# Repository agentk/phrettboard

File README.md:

# Phrettboard v1

A simple split staggered colluminar layout ergonomic keyboard.

Design priorities:

- Wireless - Bluetooth with excellent battery life
- Compact - Small and light enough to travel while chunky enough to stay put on the desk
- Tenting - Slight tenting with ability to adjust tenting in post
- Travel - Able to throw in a backpack daily for work

## Project files and folders

The repo is essentially ergogen and zmk smashed together with little regard for preserving the GitHub actions support for the ZMK config.

## BOM

| Item | Quantity |
| --- | --- |
| M3x10 BHCS | 4 |
| M3x20 BHCS | 4 |
| [LiPo Battery 2000mAh 3.7V 113450](https://ecocell.com.au/product/lipo-2000-113450/) | 2 |
| PCB | 1 pair |
| Kailh Choc hotswap sockets | 38 |
| Kailh Choc switches of your choice | 38 |
| Keycaps of your choice to match (1U) | 38 |
| Diodes IN4148 SOD-123 | 38 |
| JST-PH 2P Side entry socket | 2 |
| Silicone dome feet 8.8mm x 2.5mm | 10 |
| NRF82840 or Nice Nano v2 dev board | 2 |
| Pin sockets - machine pin - 12pin | 4 |
| Pin headers - machine pin - 12pin | 4 |
| Nice!view LCD display | 2 |
| Pin sockets - machine pin - 5pin | 2 |
| Pin headers - machine pin - 5pin | 2 |
| EVQPUC02K 4.7*3.5*1.65 SMD Reset button | 2 |
| MSS3 SMD Sliding power switch | 2 |

## [Ergogen](https://github.com/ergogen/ergogen)

The keyboard layout is built in Ergogen, then routed in Kicad.

To modify the layout:

```shell
cd ergogen
make
```

This will generate files into the `ergogen/output/` folder for both outlines and PCBs. It will overwrite any existing routed PCBs and will require you to reroute again.

## 3D Printing

The 3D printed parts were generated in Fusion 360 based off the PCB step file exported from Kicad. The priority was a form fitting case with some minor tenting which conveniently worked out well to allow space underneath for a large battery alongside the controller. The two inner feet can also be removed to reveal extra heatset inserts that support using M3 screws to increase the hight for extra tenting.

The glamour shots all featue cases FDM printed in ABS and resing printed keycaps. If you decide to print your own keycaps check out [KLP Lame](https://www.printables.com/model/552557-klp-lame-kailh-low-profile-choc-keycaps) for good sculpted keycaps (designed for resin) and [Nijuni Keycaps](https://www.printables.com/model/429659) for flatter keycaps (designed for FDM).

If printing the case in ABS I recommend using scaling X & Y by 100.5% to compensate for material shrinkage.

The travel case is designed to be printed in TPU. It prints well in quite flexible TPU and has a lot of give in it. If printing in a different material you will most likely need to scale the model bigger or smaller.

## [ZMK firmware](https://zmk.dev/docs)

To setup the build environment with Docker installed, run:

```shell
cd zmk-config
./zmk.sh build-docker
```

The typical workflow to modify the keymap is to use the [keymap editor](https://nickcoutsos.github.io/keymap-editor/), select the Clipboard source with keyboard type of custom, paste in the contents of `zmk-config/boards/shields/phrett/phrett.json` into the layout field and `zmk-config/boards/shields/phrett/phrett.keymap` into the keymap field. Modify the keyboard layout as desired, click 'Copy updated keymap' and paste it back into the local keymap.

From there the firmware can be rebuilt using:

```shell
cd zmk-config
make
```

Then connect each keyboard half one at a time, put them into bootloader mode by double tapping reset, then copying to approperate firmware from `zmk-config/artifacts/phrett_{left,right}.uf2` to the now mounted controller volume.

## License

<p xmlns:cc="http://creativecommons.org/ns#" xmlns:dct="http://purl.org/dc/terms/"><a property="dct:title" rel="cc:attributionURL" href="https://github.com/agentk/phrettboard">Phrettboard v1</a> by <a rel="cc:attributionURL dct:creator" property="cc:attributionName" href="https://github.com/agentk">Karl Bowden</a> is licensed under <a href="https://creativecommons.org/licenses/by-sa/4.0/?ref=chooser-v1" target="_blank" rel="license noopener noreferrer" style="display:inline-block;">CC BY-SA 4.0</a></p>

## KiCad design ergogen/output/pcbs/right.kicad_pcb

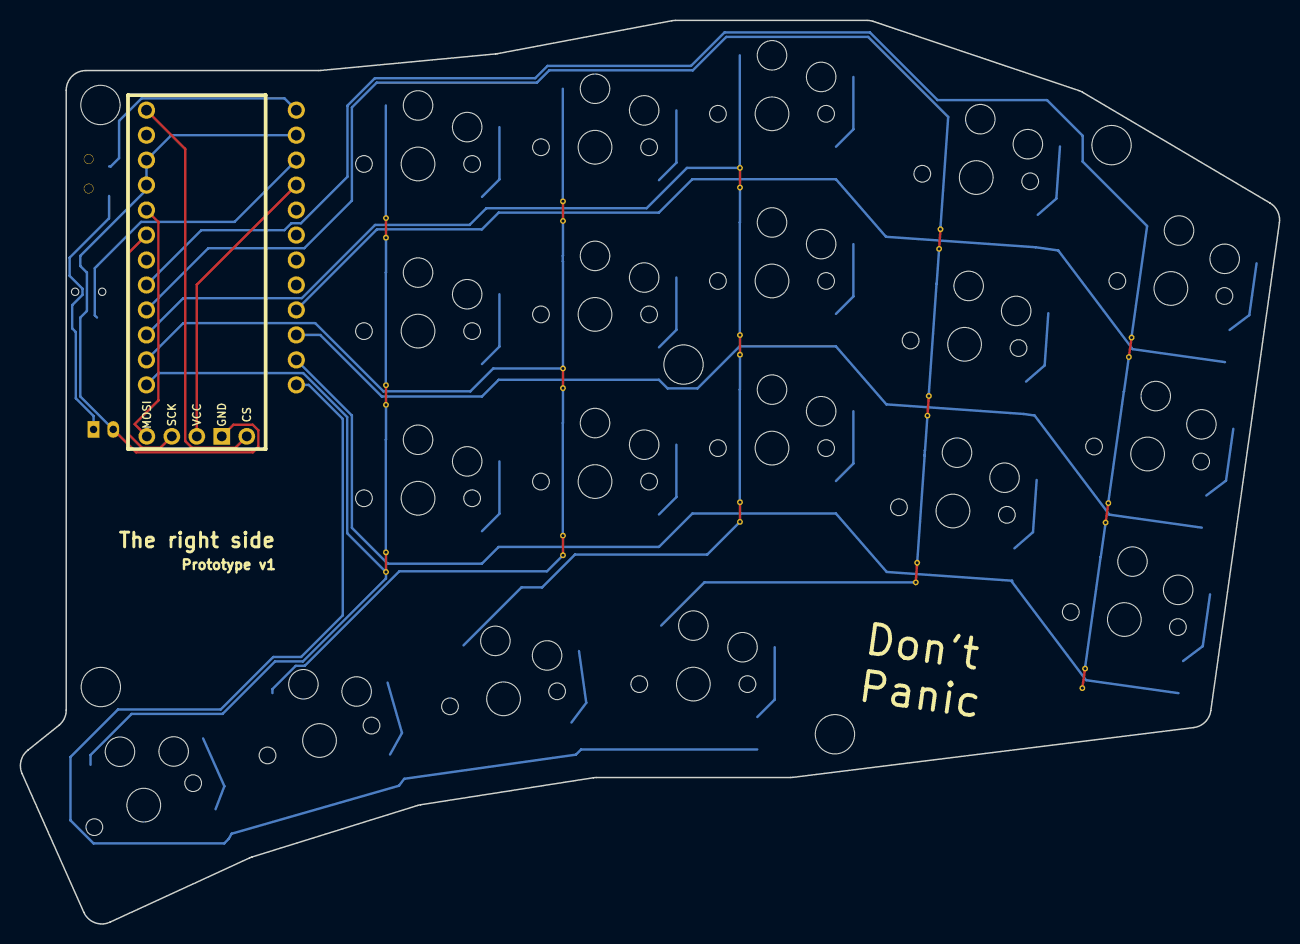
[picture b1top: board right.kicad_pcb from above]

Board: 2 copper layers, 128.1 x 91.9 mm, 43 parts (0 on the bottom side), 36 nets.

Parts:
B1: Panasonic_EVQPUL_EVQPUC
D1, D2, D3, D4, D5, D6, D7, D8, D9, D10, D11, D12, D13, D14, D15, D16, D17, D18, D19: ComboDiode
JST1: JST_PH_S2B-PH-K_02x2.00mm_Angled
MCU1: nice_nano
S1, S2, S3, S4, S5, S6, S7, S8, S9, S10, S11, S12, S13, S14, S15, S16, S17, S18, S19: PG1350
T1: SPDT_C128955
niceView1: niceView; niceView_headers

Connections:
GND: B1.1, JST1.2, MCU1.3, MCU1.4, MCU1.23, niceView1.2
P006: MCU1.1, niceView1.1
P009: D16.1, D17.1, D18.1, D19.1, MCU1.13
P010: D1.1, D4.1, D7.1, D10.1, D13.1, MCU1.14
P011: MCU1.10, S7.1, S8.1, S9.1, S17.1
P017: MCU1.5, niceView1.5
P020: MCU1.6, niceView1.4
P024: MCU1.8, S1.1, S2.1, S3.1
P100: MCU1.9, S4.1, S5.1, S6.1, S16.1
P104: MCU1.11, S10.1, S11.1, S12.1, S18.1
P106: MCU1.12, S13.1, S14.1, S15.1, S19.1
P111: D2.1, D5.1, D8.1, D11.1, D14.1, MCU1.15
P113: D3.1, D6.1, D9.1, D12.1, D15.1, MCU1.16
RAW: MCU1.24, T1.2
RST: B1.2, MCU1.22
VCC: MCU1.21, niceView1.3
mirror_index_bottom: D10.2, S10.2
mirror_index_home: D11.2, S11.2
mirror_index_top: D12.2, S12.2
mirror_inner_bottom: D13.2, S13.2
mirror_inner_home: D14.2, S14.2
mirror_inner_top: D15.2, S15.2
mirror_middle_bottom: D7.2, S7.2
mirror_middle_home: D8.2, S8.2
mirror_middle_top: D9.2, S9.2
mirror_pinky_bottom: D1.2, S1.2
mirror_pinky_home: D2.2, S2.2
mirror_pinky_top: D3.2, S3.2
mirror_ring_bottom: D4.2, S4.2
mirror_ring_home: D5.2, S5.2
mirror_ring_top: D6.2, S6.2
mirror_thumb1_cluster: D16.2, S16.2
mirror_thumb2_cluster: D17.2, S17.2
mirror_thumb3_cluster: D18.2, S18.2
mirror_thumb4_cluster: D19.2, S19.2
pos: JST1.1, T1.1

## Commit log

2024-08-31 Updated keymaps
